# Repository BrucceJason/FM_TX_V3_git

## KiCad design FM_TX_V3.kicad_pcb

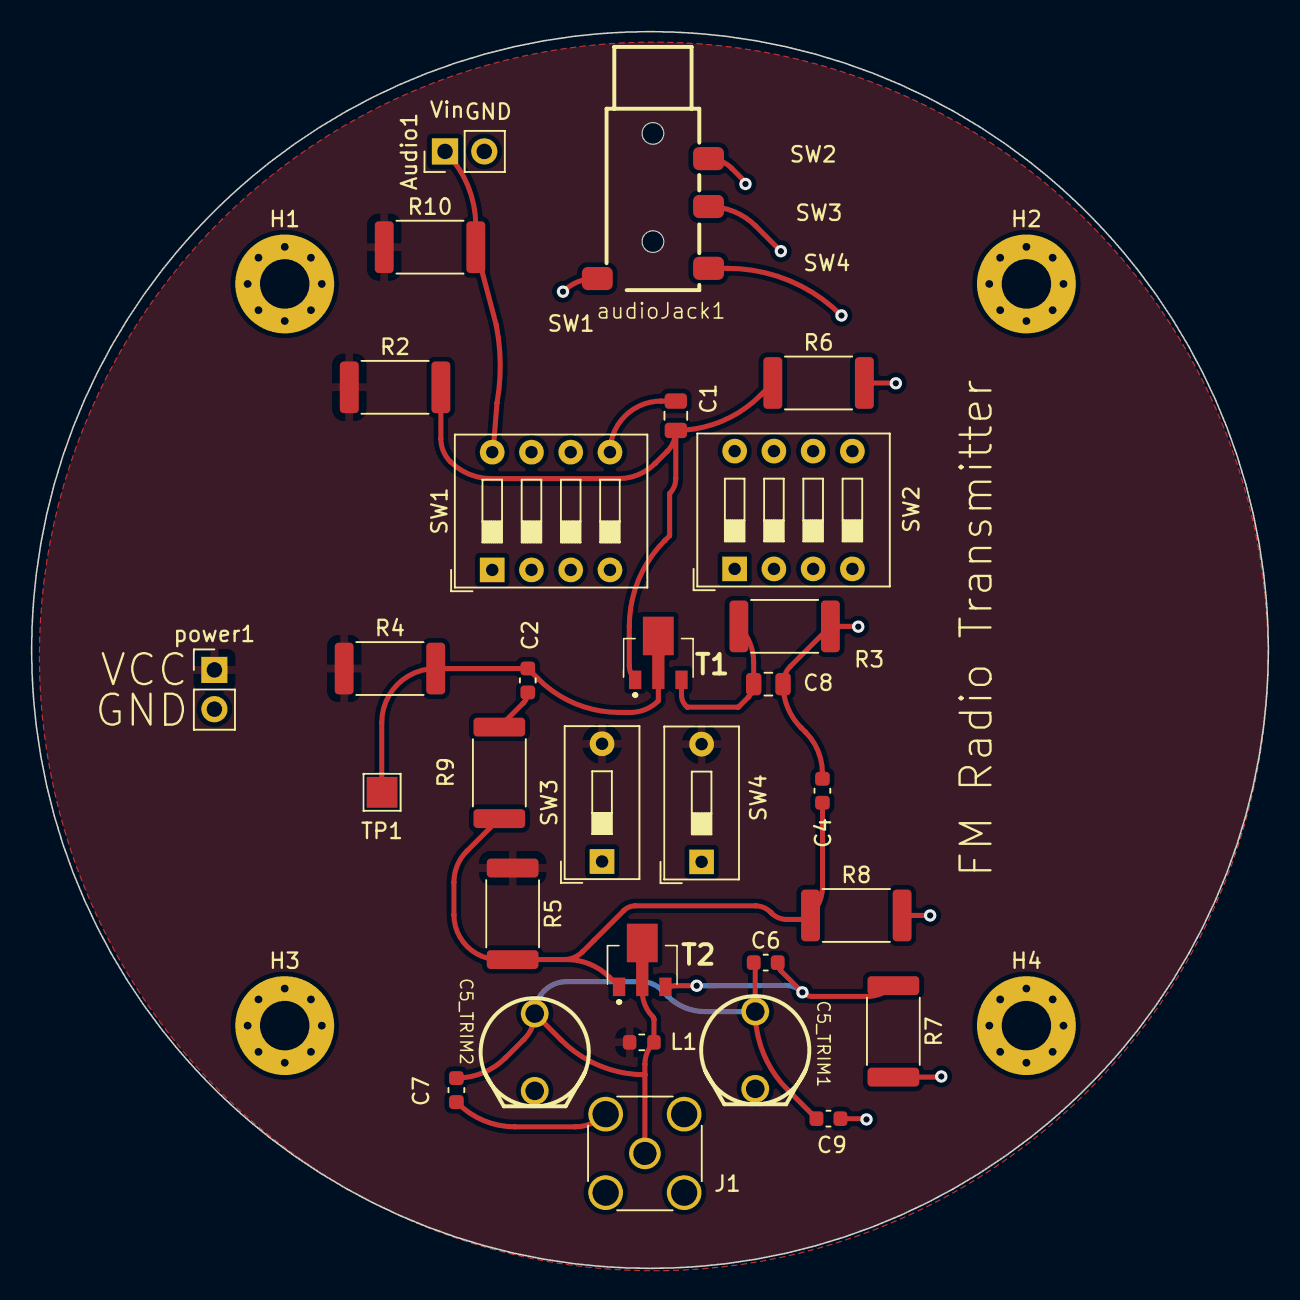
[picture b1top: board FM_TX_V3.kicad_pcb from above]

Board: 6 copper layers, 80.0 x 80.0 mm, 34 parts (0 on the bottom side), 16 nets.

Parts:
Audio1: Conn_01x02; PinHeader_1x02_P2.54mm_Vertical
C1, C8: 10u; C_0805_2012Metric
C2: 2.2u; C_0603_1608Metric
C4: 0.1u; C_0603_1608Metric
C5_TRIM1, C5_TRIM2: 20p; trimmer_cap_through_hole
C6: 4.7p; C_0603_1608Metric
C7: 2p; C_0603_1608Metric
C9: .1u; C_0603_1608Metric
H1, H2, H3, H4: MountingHole_Pad; MountingHole_3.2mm_M3_Pad_Via
J1: Conn_Coaxial; SMA_Amphenol_132134_Vertical
L1: 0.1u; L_0603_1608Metric
R2: 15k; R_2512_6332Metric
R3, R5: 4.7k; R_2512_6332Metric
R4: 10k; R_2512_6332Metric
R6: 6.8k; R_2512_6332Metric
R7: 220; R_2512_6332Metric
R8: 2.2k; R_2512_6332Metric
R9, R10: 1k; R_2512_6332Metric
SW1, SW2: SW_DIP_x04; SW_DIP_SPSTx04_Slide_9.78x12.34mm_W7.62mm_P2.54mm
SW3, SW4: SW_DIP_x01; SW_DIP_SPSTx01_Slide_9.78x4.72mm_W7.62mm_P2.54mm
T1, T2: BFQ_19S_H6327; BFQ19SH6327
TP1: TestPoint; TestPoint_Pad_2.0x2.0mm
audioJack1: audio_jack_3.5mm
power1: Conn_01x02; PinHeader_1x02_P2.54mm_Vertical

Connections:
/Emitter: C6.2, R7.1, T2.3 (E)
/Q1C: C2.1, R4.2, T1.2 (C_1), T1.4 (C_2), TP1.1
/Q2C: C5_TRIM1.2, C5_TRIM2.2, C6.1, C7.1, C9.1, J1.1 (In), L1.2, T2.2 (C_1), T2.4 (C_2)
/sw1: SW1.1, SW2.1, audioJack1.1
/sw2: SW1.2, SW2.2, audioJack1.2
/sw3: SW1.3, SW2.3, audioJack1.3
/sw4: SW1.4, SW2.4, audioJack1.4
GND: Audio1.2, C4.2, C7.2, C8.2, C9.2, H1.1, H2.1, H3.1, H4.1, J1.2 (Ext), R3.2, R6.2, R7.2, R8.2, SW2.5, SW2.6, SW2.7, SW2.8, power1.2
unnamed: C2.2, R9.1
unnamed: C5_TRIM1.1, SW4.1
unnamed: C5_TRIM2.1, SW3.1
unnamed: C1.2, R2.2, R6.1, T1.1 (B)
unnamed: C8.1, R3.1, T1.3 (E)
unnamed: C4.1, R5.2, R8.1, R9.2, T2.1 (B)
VCC: L1.1, R2.1, R4.1, R5.1, R10.1, SW3.2, SW4.2, power1.1
Vin: Audio1.1, C1.1, R10.2, SW1.5, SW1.6, SW1.7, SW1.8

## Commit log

2024-08-29 FM transmitter version 3
2024-08-30 Add asxc simulation file
